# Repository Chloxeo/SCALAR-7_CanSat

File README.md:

# SCALAR-7_CanSat

Electronics board of the CanSat carried by **SCALAR-7**, a two-stage rocket launched at **C'Space 2026**.
The board runs an **aerosol counting** experiment (PMS5003 sensor), complemented by pressure and temperature measurements, tracks the CanSat's position with GNSS and downlinks its data to the ground over LoRa.

---
## Table of contents

- [Board features](#board-features)
- [Architecture](#architecture)
  - [Power supply](#power-supply)
  - [Microcontroller](#microcontroller)
  - [Telemetry](#telemetry)
  - [Experiments](#experiments)
  - [Indicators](#indicators)
- [Main components](#main-components)
- [Repository structure](#repository-structure)

---

## Board features

| Function | Implementation |
|---|---|
| Processing / logging | STM32F405RGT6 (Cortex-M4F, 168 MHz), 12 MHz HSE + 32.768 kHz LSE crystals |
| Aerosol measurement | Connector for a **Plantower PMS5003** particle sensor (UART4) |
| Pressure measurement | **Infineon KP466** barometer (SPI3) |
| Temperature measurement | **DS18B20** probe (1-Wire) |
| Positioning | **u-blox MAX-M10S** GNSS module (USART6 or I²C1) |
| Ground link | **RFM95W** LoRa 868 MHz module (SPI1) |
| Power supply | Protected battery input (reverse polarity, overcurrent), 3.3 V and 5 V regulators |
| PC interface | USB-C (native STM32 USB FS, VBUS sensing), VCP serial port |
| Debug | 14-pin STLINK connector (SWD + SWO + VCP), reset button, BOOT0 jumper |
| Indicators | Buzzer, status LEDs (3V3, 5V, PPS) |

---

## Architecture

```mermaid
flowchart LR
    BAT[Battery<br/>J6] --> PROT[Switch SW2<br/>+ reverse-polarity P-MOS<br/>+ polyfuse]
    PROT --> REG33[LD1117 3V3]
    PROT --> REG5[L7805 5V]

    REG33 --> MCU[STM32F405RGT6]
    REG33 --> GPS[MAX-M10S<br/>GNSS]
    REG33 --> LORA[RFM95W<br/>LoRa 868 MHz]
    REG33 --> BARO[KP466<br/>barometer]
    REG33 --> TEMP[DS18B20<br/>temperature]
    REG5 --> PMS[PMS5003<br/>aerosols]
    REG5 --> BUZ[Buzzer]

    GPS <-- USART6 / I2C1 --> MCU
    LORA <-- SPI1 --> MCU
    BARO <-- SPI3 --> MCU
    TEMP <-- 1-Wire --> MCU
    PMS <-- UART4 --> MCU
    USB[USB-C] <-- USB FS --> MCU
    STLINK[STLINK<br/>SWD / VCP] <--> MCU
```

### Power supply

The board is powered by an external battery through a switch. The input is protected against reverse polarity (P-MOSFET) and overcurrent (polyfuse), then two linear regulators generate the **3V3** rail (logic, sensors, radio) and the **5V** rail (aerosol sensor, buzzer).

### Microcontroller

An **STM32F405** handles sensor acquisition, GNSS management and LoRa frame transmission. It is clocked by a 12 MHz crystal, with a 32.768 kHz crystal for the RTC. The board is programmed and debugged through an **STLINK** connector (SWD + VCP serial port) and also provides a **USB-C** port, a reset button and a BOOT0 jumper.

### Telemetry

- **GNSS**: a **u-blox MAX-M10S** module provides the position and a PPS signal. It connects to an external antenna through an SMA connector and keeps its data in memory thanks to a backup battery.
- **LoRa**: an **RFM95W** module (868 MHz, SPI) sends the data to the ground through a patch antenna on a U.FL connector.

### Experiments

- **Aerosols**: **PMS5003** particle sensor, connected over UART.
- **Pressure**: **KP466** barometer over SPI.
- **Temperature**: **DS18B20** probe over 1-Wire.

### Indicators

An RGB LED and a buzzer show the system status, and indicator LEDs show that the power input and the 3V3 / 5V rails are present.

---

## Main components

| Ref. | Component | Function |
|---|---|---|
| U2 | STM32F405RGT6 | Microcontroller |
| U1 | u-blox MAX-M10S-00B | GNSS receiver |
| U3 | HopeRF RFM95W-868S2 | LoRa 868 MHz transceiver |
| IC2 | Infineon KP466PXTMA1 | Pressure sensor |
| U4 | Maxim DS18B20+ | Temperature sensor |
| IC1 | ST LD1117DT33TR | 3.3 V regulator |
| IC3 | ST L7805CDT-TR | 5 V regulator |
| Q2 | Vishay SQD50P04-13L | Reverse-polarity protection |
| F1 | Littelfuse 1812L260/16MR | Polyfuse |
| Q3 | IRLZ34NPBF | Buzzer driver |
| Q1 | 2N7002 | VBUS sensing |
| XTAL1 | ECS-120-8-33-JGN-TR | 12 MHz crystal |
| Y1 | ECS-.327-6-34RR-TR | 32.768 kHz crystal |
| LED1 | Würth 150141M173100 | RGB LED |
| SW1 | TE 1825910-6 | Reset button |
| SW2 | 25139NAH | Power switch |

---

## Repository structure

```
SCALAR-7_CanSat/
├── hardware/          # KiCad files and libraries
├── images/
├── schematic.pdf
└── README.md
```

---

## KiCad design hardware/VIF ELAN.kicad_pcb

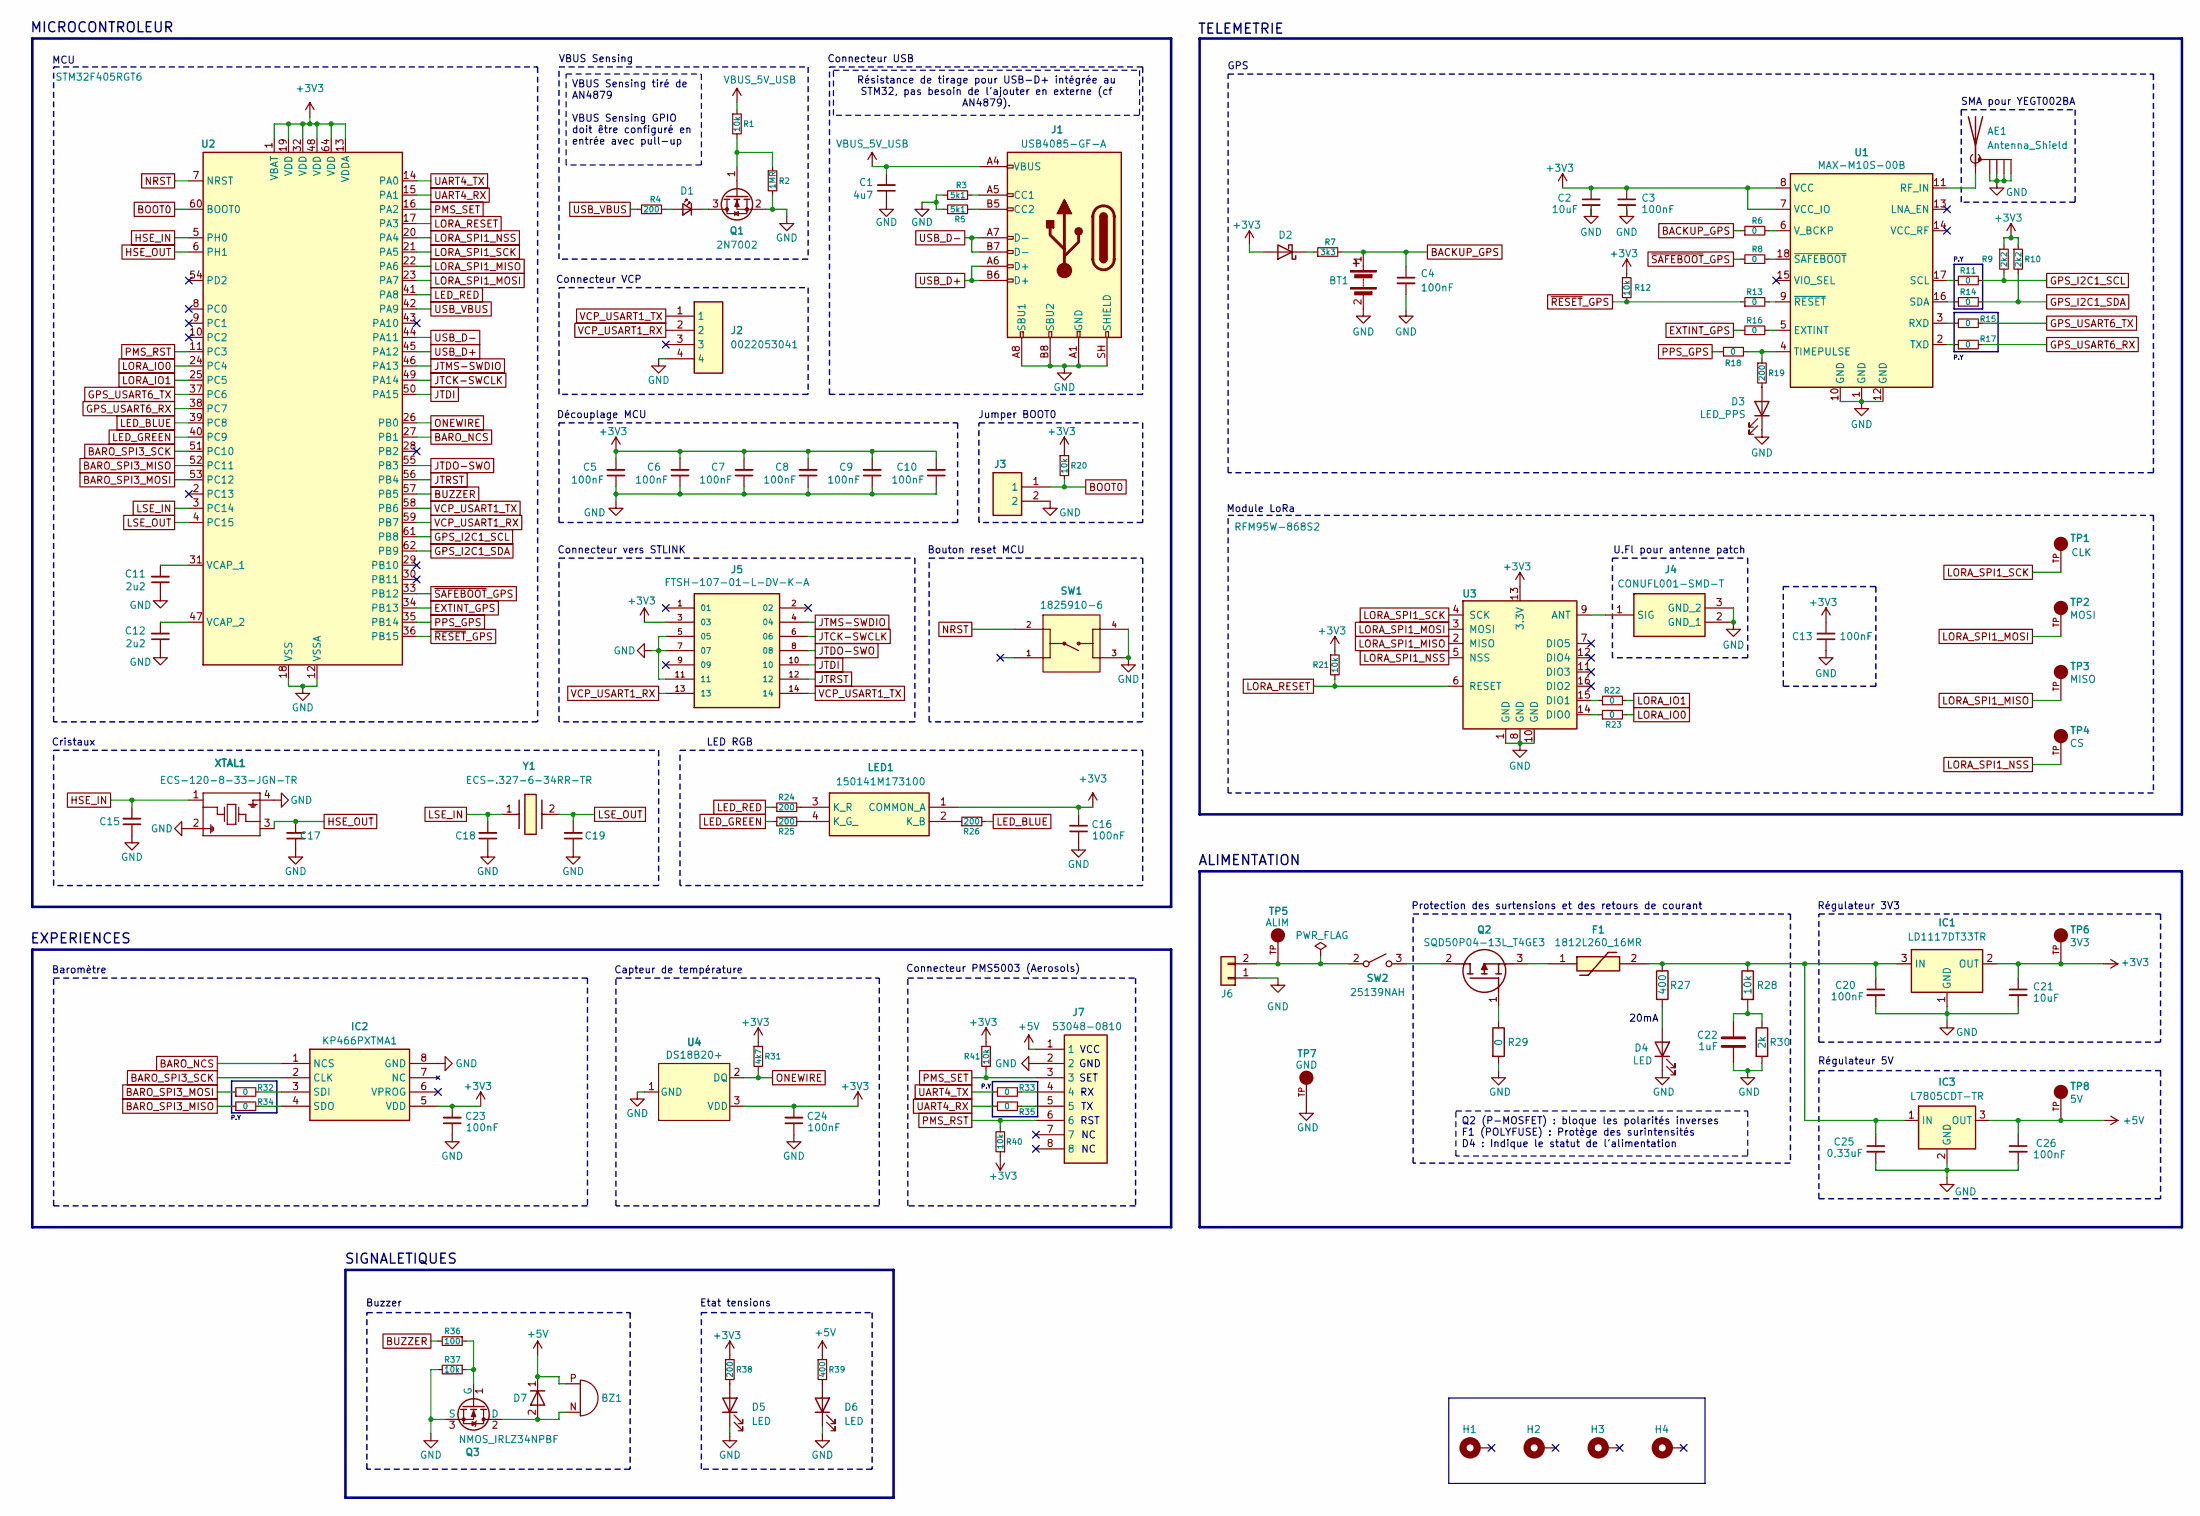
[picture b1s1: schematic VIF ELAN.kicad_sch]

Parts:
AE1: Antenna_Shield; SMA_coude
BT1: 6.8mm 3.3V; pile btn
BZ1: Buzzer; buzzer CUI_CEM-1206S
C1: 4u7; C_0603_1608Metric_Pad1.08x0.95mm_HandSolder
C2, C21: 10uF; C_0603_1608Metric_Pad1.08x0.95mm_HandSolder
C3, C4, C5, C6, C7, C8, C9, C10, C13, C16, C20, C23, C24, C26: 100nF; C_0603_1608Metric_Pad1.08x0.95mm_HandSolder
C11, C12: 2u2; C_0603_1608Metric_Pad1.08x0.95mm_HandSolder
C15, C17, C18, C19: C_0603_1608Metric_Pad1.08x0.95mm_HandSolder
C22: 1uF; C_0603_1608Metric_Pad1.08x0.95mm_HandSolder
C25: 0,33uF; C_0603_1608Metric_Pad1.08x0.95mm_HandSolder
D1, D4, D5, D6: LED; LED_0805_2012Metric_Pad1.15x1.40mm_HandSolder
D2: bat54 SOD3716X135N
D3: LED_PPS; LED_0805_2012Metric_Pad1.15x1.40mm_HandSolder
D7: D; D_0805_2012Metric_Pad1.15x1.40mm_HandSolder
F1: 1812L260_16MR; 1812L010DR; Mouser Part Number 576-1812L260/16MR
H1, H2, H3, H4: MountingHole_Pad; MountingHole_2.2mm_M2_DIN965_Pad_TopBottom
IC1: LD1117DT33TR; Mouser Part Number 511-LD1117DT33-TR
IC2: KP466PXTMA1; Mouser Part Number 726-KP466PXTMA1
IC3: L7805CDT-TR; L7805CDTTR; Mouser Part Number 511-L7805CDT-TR
J1: USB4085-GF-A; USB_C_Receptacle_GCT_USB4085; Manufacturer_Part_Number USB4085-GF-A
J2: 0022053041; 22053041; Manufacturer_Part_Number 0022053041; Mouser Part Number N/A
J3: TSW-102-07-G-S; jumper TSW-102-XX-YY-S; Manufacturer_Part_Number TSW-102-07-G-S; Mouser Part Number 200-TSW10207GS
J4: CONUFL001-SMD-T; CONUFL001SMDT; Mouser Part Number N/A
J5: FTSH-107-01-L-DV-K-A; FTSH-107-XX-YYY-DV-K-A; PARTREV H
J6: Batterie; SHDR2W100P0X508_1X2_1216X850X1215P
J7: 53048-0810; 530480810; Manufacturer_Part_Number 53048-0810; Mouser Part Number 538-53048-0810
LED1: 150141M173100; LED_RGB_Wuerth-PLCC4_3.2x2.8mm_150141M173100; Manufacturer_Part_Number 150141M173100; Mouser Part Number 710-150141M173100
Q1: 2N7002; SOT-23; Manufacturer_Part_Number DS18B20+
Q2: SQD50P04-13L_T4GE3; Q2 SQD50P0413L_T4GE3; Mouser Part Number 78-SQD50P04-13LT4GE3
Q3: NMOS_IRLZ34NPBF; TO-220-3_Horizontal_TabDown
R1, R12, R20, R21, R28, R37, R40, R41: 10k; R_0603_1608Metric_Pad0.98x0.95mm_HandSolder
R2: 1MR; R_0603_1608Metric_Pad0.98x0.95mm_HandSolder
R3, R5: 5k1; R_0603_1608Metric_Pad0.98x0.95mm_HandSolder
R4, R19, R24, R25, R26, R38: 200; R_0603_1608Metric_Pad0.98x0.95mm_HandSolder
R6, R8, R11, R13, R14, R15, R16, R17, R18, R22, R23, R29, R32, R33, R34, R35: 0; R_0603_1608Metric_Pad0.98x0.95mm_HandSolder
R7: 3k3; R_0603_1608Metric_Pad0.98x0.95mm_HandSolder
R9, R10: 2k2; R_0603_1608Metric_Pad0.98x0.95mm_HandSolder
R27, R39: 400; R_0603_1608Metric_Pad0.98x0.95mm_HandSolder
R30: 2k; R_0603_1608Metric_Pad0.98x0.95mm_HandSolder
R31: 4k7; R_0603_1608Metric_Pad0.98x0.95mm_HandSolder
R36: 100; R_0603_1608Metric_Pad0.98x0.95mm_HandSolder
SW1: 1825910-6; 18259106; PARTREV C10
SW2: 25139NAH
TP1: CLK; 5003; PARTREV B
TP2: MOSI; 5003; PARTREV B
TP3: MISO; 5003; PARTREV B
TP4: CS; 5003; PARTREV B
TP5: ALIM; 5003; PARTREV B
TP6: 3V3; 5003; PARTREV B
TP7: GND; 5003; PARTREV B
TP8: 5V; 5003; PARTREV B
U1: MAX-M10S-00B; ublox_MAX
U2: STM32F405RGT6; LQFP-64_10x10mm_P0.5mm; Manufacturer_Part_Number STM32F405RGT6
U3: RFM95W-868S2; HOPERF_RFM9XW_SMD; Manufacturer_Part_Number RFM95W-868S2
U4: DS18B20+; temp 21-0248A_MXM; Manufacturer_Part_Number DS18B20+
XTAL1: ECS-120-8-33-JGN-TR; ECS-120-8-33-JGN-TR_ECS; Manufacturer_Part_Number ECS-120-8-33-JGN-TR
Y1: ECS-.327-6-34RR-TR; ECS32712534RRTR; Manufacturer_Part_Number ECS-.327-6-34RR-TR; Mouser Part Number 520-.327-6-34RRT

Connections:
+3V3: C2.1, C3.1, C5.2, C6.2, C7.2, C8.2, C9.2, C10.2, C13.2, C16.2, C21.1, C23.2, C24.2, D2.2 (A), IC1.2 (OUT), IC2.5 (VDD), J5.3, LED1.1 (COMMON_A), R9.1, R10.1, R12.1, R20.1, R21.1, R31.1, R38.1, R40.1, R41.1, TP6.TP, U1.7 (VCC_IO), U1.8 (VCC), U2.1 (VBAT), U2.13 (VDDA), U2.19 (VDD), U2.32 (VDD), U2.48 (VDD), U2.64 (VDD), U3.13 (3.3V), U4.3 (VDD)
+5V: BZ1.P (-), C26.1, D7.1 (K), IC3.3 (OUT), J7.1, R39.1, TP8.TP
BACKUP_GPS: BT1.1 (+), C4.1, R6.1, R7.2
BARO_NCS: IC2.1 (NCS), U2.27 (PB1)
BARO_SPI3_MISO: R34.1, U2.52 (PC11)
BARO_SPI3_MOSI: R32.1, U2.53 (PC12)
BARO_SPI3_SCK: IC2.2 (CLK), U2.51 (PC10)
BOOT0: J3.1, R20.2, U2.60 (BOOT0)
BUZZER: R36.2, U2.57 (PB5)
EXTINT_GPS: R16.1, U2.34 (PB13)
GND: AE1.2 (GND), AE1.3 (GND), AE1.4 (GND), AE1.5 (GND), BT1.2 (-), C1.1, C2.2, C3.2, C4.2, C5.1, C6.1, C7.1, C8.1, C9.1, C10.1, C11.1, C12.1, C13.1, C15.1, C16.1, C17.1, C18.1, C19.1, C20.2, C21.2, C22.2, C23.1, C24.1, C25.2, C26.2, D3.1 (K), D4.1 (K), D5.1 (K), D6.1 (K), IC1.1 (GND), IC2.8 (GND), IC3.2 (GND), J1.A1 (GND), J1.A8 (SBU1), J1.B8 (SBU2), J1.SH (SHIELD), J2.4, J3.2, J4.2 (GND_1), J4.3 (GND_2), J5.5, J5.7, J5.11, J6.1, J7.2, Q1.2 (S), Q3.3 (S), R2.2, R3.1, R5.1, R29.2, R30.2, R37.2, SW1.1, SW1.3, SW1.4, TP7.TP, U1.1 (GND), U1.10 (GND), U1.12 (GND), U2.12 (VSSA), U2.18 (VSS), U3.1 (GND), U3.8 (GND), U3.10 (GND), U4.1 (GND), XTAL1.2, XTAL1.4; also elsewhere on the board
GPS_I2C1_SCL: R9.2, R11.2, U2.61 (PB8)
GPS_I2C1_SDA: R10.2, R14.2, U2.62 (PB9)
GPS_USART6_RX: R17.2, U2.38 (PC7)
GPS_USART6_TX: R15.2, U2.37 (PC6)
HSE_IN: C15.2, U2.5 (PH0), XTAL1.1
HSE_OUT: C17.2, U2.6 (PH1), XTAL1.3
JTCK-SWCLK: J5.6, U2.49 (PA14)
JTDI: J5.10, U2.50 (PA15)
JTDO-SWO: J5.8, U2.55 (PB3)
JTMS-SWDIO: J5.4, U2.46 (PA13)
JTRST: J5.12, U2.56 (PB4)
LED_BLUE: R26.2, U2.39 (PC8)
LED_GREEN: R25.1, U2.40 (PC9)
LED_RED: R24.1, U2.41 (PA8)
LORA_IO0: R23.2, U2.24 (PC4)
LORA_IO1: R22.2, U2.25 (PC5)
LORA_RESET: R21.2, U2.17 (PA3), U3.6 (RESET)
LORA_SPI1_MISO: TP3.TP, U2.22 (PA6), U3.2 (MISO)
LORA_SPI1_MOSI: TP2.TP, U2.23 (PA7), U3.3 (MOSI)
LORA_SPI1_NSS: TP4.TP, U2.20 (PA4), U3.5 (NSS)
LORA_SPI1_SCK: TP1.TP, U2.21 (PA5), U3.4 (SCK)
LSE_IN: C18.2, U2.3 (PC14), Y1.1
LSE_OUT: C19.2, U2.4 (PC15), Y1.2
NRST: SW1.2, U2.7 (NRST); also elsewhere on the board
unnamed: AE1.1 (A), U1.11 (RF_IN)
unnamed: BZ1.N (+), D7.2 (A), Q3.2 (D)
unnamed: C22.1, R28.2, R30.1
unnamed: D1.2 (A), R4.2
unnamed: D1.1 (K), Q1.3 (D)
unnamed: D2.1 (K), R7.1
unnamed: D3.2 (A), R19.2
unnamed: D4.2 (A), R27.2
unnamed: D5.2 (A), R38.2
unnamed: D6.2 (A), R39.2
unnamed: C20.1, C25.1, F1.2, IC1.3 (IN), IC3.1 (IN), R27.1, R28.1
unnamed: IC2.3 (SDI), R32.2
unnamed: IC2.4 (SDO), R34.2
unnamed: J1.A5 (CC1), R3.2
unnamed: J1.B5 (CC2), R5.2
unnamed: J4.1 (SIG), U3.9 (ANT)
unnamed: J6.2, SW2.2 (A), TP5.TP
unnamed: J7.4, R33.2
unnamed: J7.5, R35.2
unnamed: LED1.2 (K_B), R26.1
unnamed: LED1.4 (K_G_), R25.2
unnamed: LED1.3 (K_R), R24.2
unnamed: Q1.1 (G), R1.2, R2.1
unnamed: Q2.2 (D), SW2.3 (B)
unnamed: Q2.1 (G), R29.1
unnamed: F1.1, Q2.3 (S)
unnamed: Q3.1 (G), R36.1, R37.1
unnamed: R16.2, U1.5 (EXTINT)
unnamed: R15.1, U1.3 (RXD)
unnamed: R11.1, U1.17 (SCL)
unnamed: R14.1, U1.16 (SDA)
unnamed: R18.2, R19.1, U1.4 (TIMEPULSE)
unnamed: R17.1, U1.2 (TXD)
unnamed: R6.2, U1.6 (V_BCKP)
unnamed: R13.2, U1.9 (~RESET)
unnamed: R8.2, U1.18 (~SAFEBOOT)
unnamed: C11.2, U2.31 (VCAP_1)
unnamed: C12.2, U2.47 (VCAP_2)
unnamed: R23.1, U3.14 (DIO0)
unnamed: R22.1, U3.15 (DIO1)
ONEWIRE: R31.2, U2.26 (PB0), U4.2 (DQ)
PMS_RST: J7.6, R40.2, U2.11 (PC3)
PMS_SET: J7.3, R41.2, U2.16 (PA2)
PPS_GPS: R18.1, U2.35 (PB14)
UART4_RX: R35.1, U2.15 (PA1)
UART4_TX: R33.1, U2.14 (PA0)
USB_D+: J1.A6 (D+), J1.B6 (D+), U2.45 (PA12)
USB_D-: J1.A7 (D-), J1.B7 (D-), U2.44 (PA11)
USB_VBUS: R4.1, U2.42 (PA9)
VBUS_5V_USB: C1.2, J1.A4 (VBUS), R1.1
VCP_USART1_RX: J2.2, J5.13, U2.59 (PB7)
VCP_USART1_TX: J2.1, J5.14, U2.58 (PB6)
~RESET_GPS: R12.2, R13.1, U2.36 (PB15)
~SAFEBOOT_GPS: R8.1, U2.33 (PB12)

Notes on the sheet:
Découplage MCU
P.Y
SMA pour YEGT002BA
Etat tensions
VCC
Baromètre
TELEMETRIE
GND
Régulateur 5V
Module LoRa
Régulateur 3V3
GPS
Protection des surtensions et des retours de courant
Cristaux
Connecteur PMS5003 (Aerosols)
Jumper BOOT0
U.Fl pour antenne patch
LED RGB
Connecteur USB
Buzzer
SET
Capteur de température
EXPERIENCES
MCU
MICROCONTROLEUR
Connecteur VCP
Bouton reset MCU
ALIMENTATION
SIGNALETIQUES
20mA
VBUS Sensing
Connecteur vers STLINK
RST
VBUS Sensing tiré de AN4879 VBUS Sensing GPIO doit être configuré en entrée avec pull-up
Q2 (P-MOSFET) : bloque les polarités inverses F1 (POLYFUSE) : Protège des surintensités D4 : Indique le statut de l'alimentation
Résistance de tirage pour USB-D+ intégrée au STM32, pas besoin de l'ajouter en externe (cf AN4879).

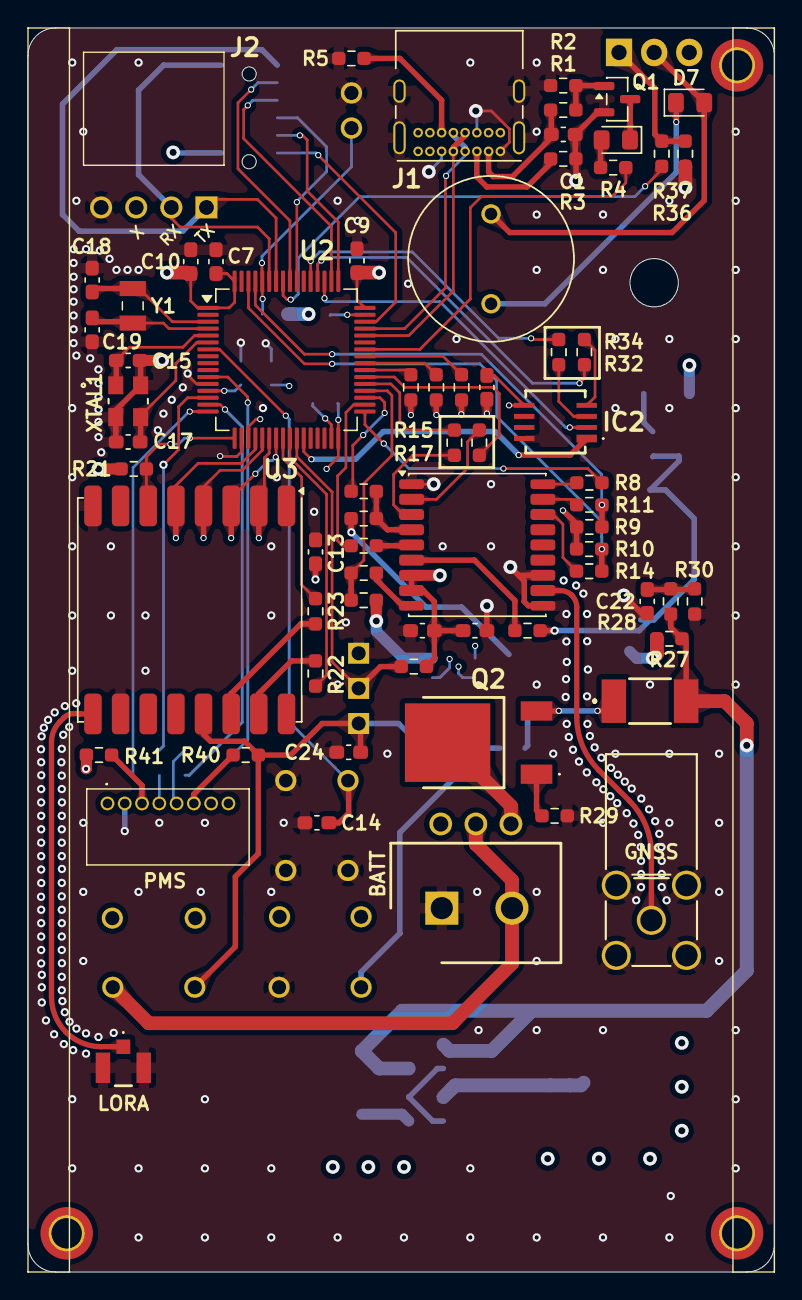
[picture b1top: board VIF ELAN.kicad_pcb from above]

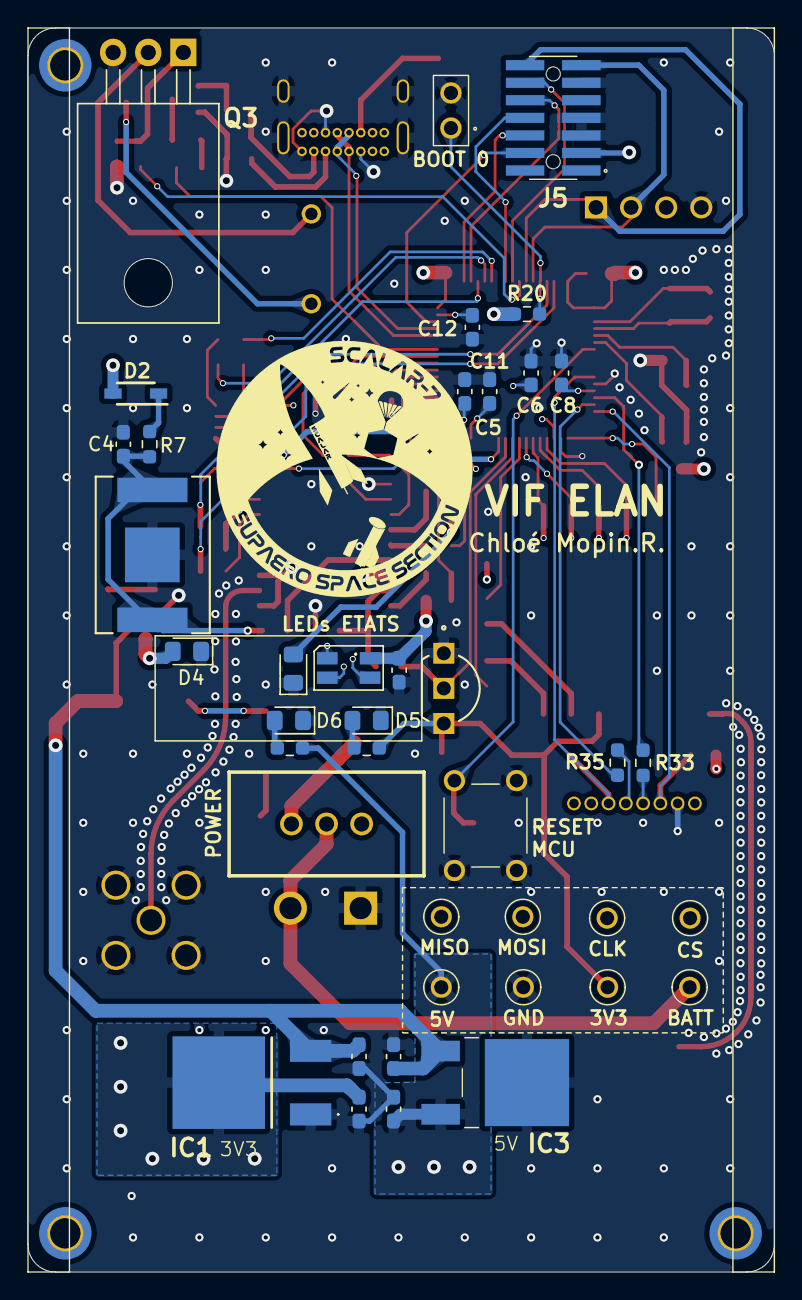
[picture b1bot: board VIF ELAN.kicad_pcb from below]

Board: 4 copper layers, 54.0 x 90.0 mm, 112 parts (40 on the bottom side), 89 nets.

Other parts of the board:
C14: 100nF; C_0603_1608Metric_Pad1.08x0.95mm_HandSolder
PMS: TestPoint_Pad_1.0x1.0mm

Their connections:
GND: C14.1; also elsewhere on the board
NRST: C14.2; also elsewhere on the board
